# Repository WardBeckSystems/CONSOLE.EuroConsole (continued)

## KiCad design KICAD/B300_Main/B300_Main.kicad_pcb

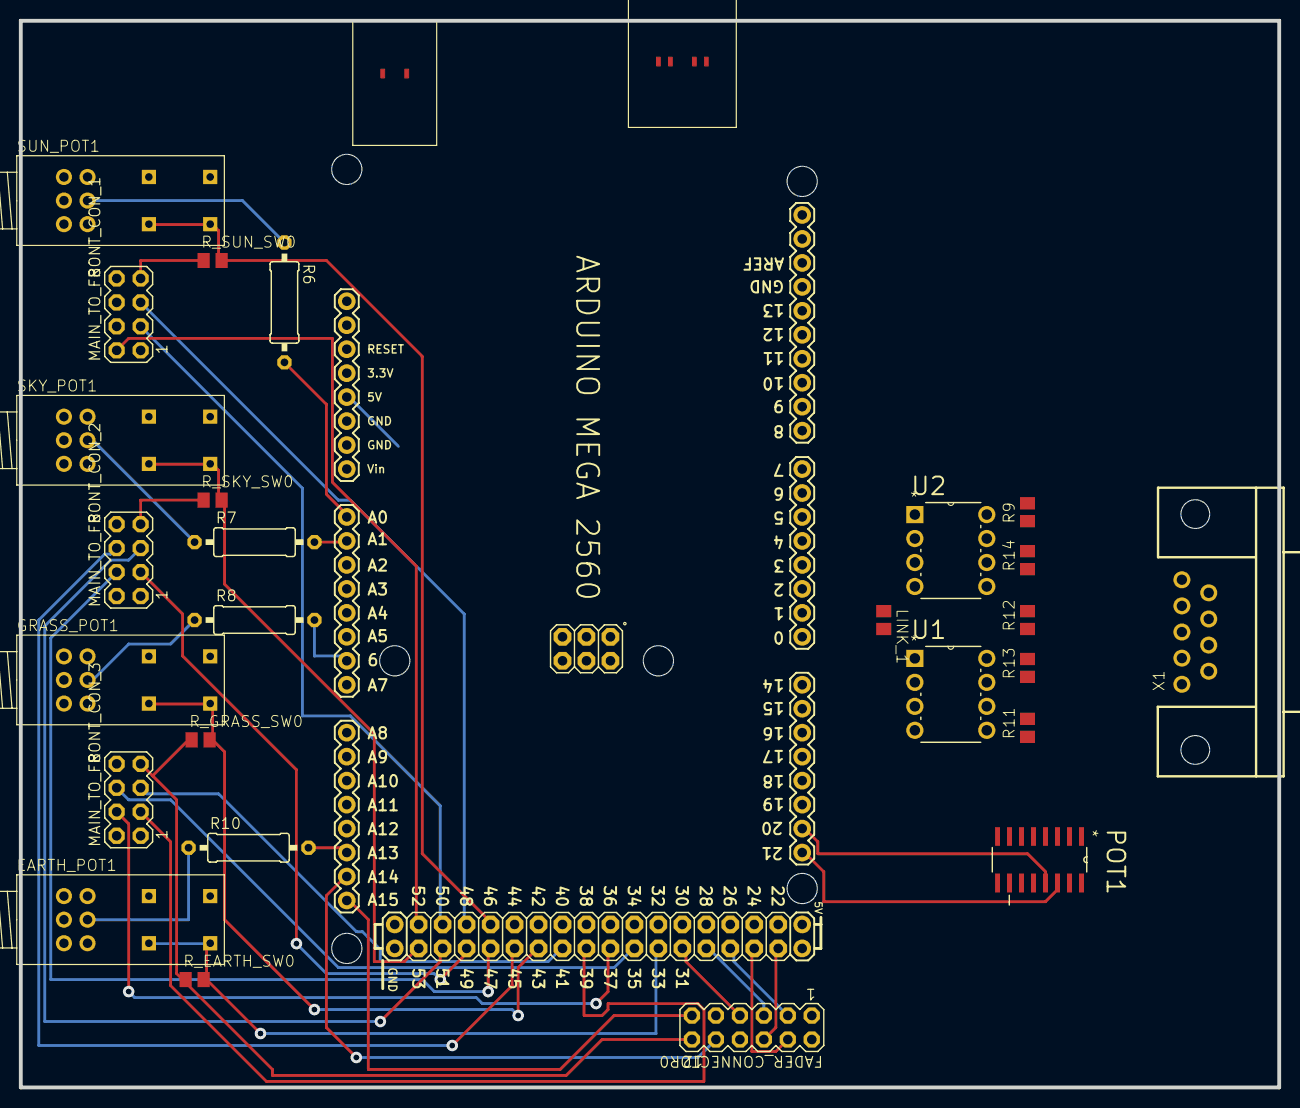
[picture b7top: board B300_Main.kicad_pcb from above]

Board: 2 copper layers, 133.3 x 113.0 mm, 27 parts (0 on the bottom side), 43 nets.

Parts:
EARTH_POT1: WBS_10-081_DUALPOT+DUALSWITCH; WBS_10-081
FADER_CONNECTOR0: MA06-2
GRASS_POT1: WBS_10-081_DUALPOT+DUALSWITCH; WBS_10-081
LINK_1: 0; M0805
MAIN_TO_FRONT_CON_1, MAIN_TO_FRONT_CON_2, MAIN_TO_FRONT_CON_3: MA04-2
PCB1: ARDUINO_MEGA2560
POT1: DS1808Z-050+; SOIC127P600X175-16N
R6, R7, R8, R10: 0309_12
R9, R11, R12, R13, R14: 10K; M0805
R_EARTH_SW0: 10K; M0805
R_GRASS_SW0: 10K; M0805
R_SKY_SW0: 10K; M0805
R_SUN_SW0: 10K; M0805
SKY_POT1: WBS_10-081_DUALPOT+DUALSWITCH; WBS_10-081
SUN_POT1: WBS_10-081_DUALPOT+DUALSWITCH; WBS_10-081
U1, U2: DS75176BN; DIP254P762X508-8
X1: D-SUB9-H3M09RA; H3M09RA

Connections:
+5V: EARTH_POT1.P$6, FADER_CONNECTOR0.12, GRASS_POT1.P$6, MAIN_TO_FRONT_CON_1.7, MAIN_TO_FRONT_CON_1.8, MAIN_TO_FRONT_CON_2.7, MAIN_TO_FRONT_CON_2.8, MAIN_TO_FRONT_CON_3.7, MAIN_TO_FRONT_CON_3.8, PCB1.5V, PCB1.<PWR>+V, POT1.16, R9.2, R12.2, R13.2, R_EARTH_SW0.1, R_GRASS_SW0.1, R_SKY_SW0.1, R_SUN_SW0.1, SKY_POT1.P$6, SUN_POT1.P$6, U1.8, U2.8
A0_FNT_POT_SUN: PCB1.A0, R6.2
A1_FNT_POT_SKY: PCB1.A1, R7.2
A6_FNT_POT_GRASS: PCB1.A6, R8.2
A12_FNT_POT_EARTH: PCB1.A12, R10.2
A14_FDR_POT_POSITION: FADER_CONNECTOR0.10, PCB1.A14
A15_FDR_POT_SLIDE: FADER_CONNECTOR0.11, PCB1.A15
D02_SCI_TX_3RC2: PCB1.2, U2.2, U2.3
D14_SCI_TX3: PCB1.14, U2.4
D15_SCI_RX3: LINK_1.2, PCB1.15, R12.1, U1.1
D20_SCI_I2C_SDA: PCB1.20, POT1.13
D21_SCI_I2C_SCL: PCB1.21, POT1.14
D22_FDR_LED_KEY_ONLY: FADER_CONNECTOR0.8, PCB1.22
D23_FDR_LED_KEY_SEL: FADER_CONNECTOR0.6, PCB1.23
D25_FDR_LED_KEY_CHON: FADER_CONNECTOR0.4, PCB1.25
D27_FDR_KEY_CHON: FADER_CONNECTOR0.3, PCB1.27
D29_FDR_KEY_SEL: FADER_CONNECTOR0.5, PCB1.29
D31_FDR_KEY_ONLY: FADER_CONNECTOR0.7, PCB1.31
D33_FNT_SW_POT_EARTH: EARTH_POT1.P$7, EARTH_POT1.P$9, PCB1.33, R_EARTH_SW0.2
D35_FNT_KEY_GRASS: MAIN_TO_FRONT_CON_3.6, PCB1.35
D37_FNT_KEY_EARTH: MAIN_TO_FRONT_CON_3.4, PCB1.37
D39_FNT_LED_KEY_EARTH: MAIN_TO_FRONT_CON_3.3, PCB1.39
D41_FNT_LED_KEY_GRASS: MAIN_TO_FRONT_CON_3.5, PCB1.41
D43_FNT_SW_POT_GRASS: GRASS_POT1.P$7, GRASS_POT1.P$9, PCB1.43, R_GRASS_SW0.2
D45_FNT_KEY_SUN: MAIN_TO_FRONT_CON_2.6, PCB1.45
D46_FNT_SW_POT_SUN: PCB1.46, R_SUN_SW0.2, SUN_POT1.P$7, SUN_POT1.P$9
D47_FNT_KEY_SKY: MAIN_TO_FRONT_CON_2.4, PCB1.47
D48_FNT_NEO_PIXEL: MAIN_TO_FRONT_CON_1.5, PCB1.48
D49_FNT_LED_KEY_SKY: MAIN_TO_FRONT_CON_2.3, PCB1.49
D50_FNT_LED_KEY_SEL: MAIN_TO_FRONT_CON_1.3, PCB1.50
D51_FNT_LED_KEY_SUN: MAIN_TO_FRONT_CON_2.5, PCB1.51
D52_FNT_KEY_SEL: MAIN_TO_FRONT_CON_1.2, PCB1.52
D53_FNT_SW_POT_SKY: PCB1.53, R_SKY_SW0.2, SKY_POT1.P$7, SKY_POT1.P$9
DB9_RS-485-RX+: R9.1, U1.6, X1.3
DB9_RS-485-RX-: R11.2, U1.7, X1.4
DB9_RS-485-TX+: R13.1, U2.6, X1.1
DB9_RS-485-TX-: R14.2, U2.7, X1.2
GND: EARTH_POT1.P$4, EARTH_POT1.P$8, EARTH_POT1.P$10, FADER_CONNECTOR0.1, GRASS_POT1.P$4, GRASS_POT1.P$8, GRASS_POT1.P$10, MAIN_TO_FRONT_CON_1.1, MAIN_TO_FRONT_CON_2.1, MAIN_TO_FRONT_CON_3.1, PCB1.<PWR>-V, PCB1.GND, PCB1.GND., PCB1.GND.., POT1.1, POT1.7, POT1.9, R11.1, R14.1, SKY_POT1.P$4, SKY_POT1.P$8, SKY_POT1.P$10, SUN_POT1.P$4, SUN_POT1.P$8, SUN_POT1.P$10, U1.2, U1.3, U1.5, U2.5
unnamed: EARTH_POT1.P$5, R10.1
unnamed: R7.1, SKY_POT1.P$5
unnamed: R6.1, SUN_POT1.P$5
unnamed: GRASS_POT1.P$5, R8.1
unnamed: LINK_1.1, U2.1

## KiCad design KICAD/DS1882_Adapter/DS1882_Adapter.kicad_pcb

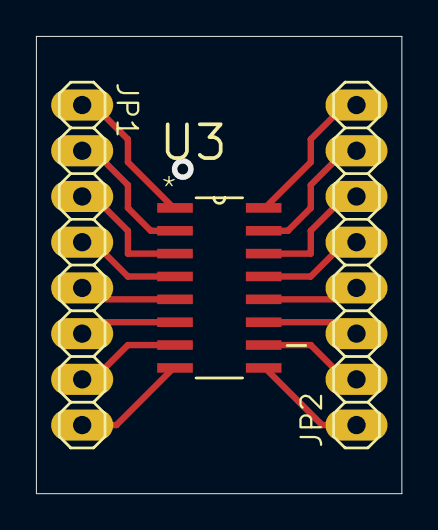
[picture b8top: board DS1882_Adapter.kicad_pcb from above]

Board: 2 copper layers, 20.3 x 25.4 mm, 3 parts (0 on the bottom side), 16 nets.

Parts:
JP1, JP2: 1X08
U3: DS1808Z-050+; SOIC127P600X175-16N

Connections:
unnamed: JP1.1, U3.1
unnamed: JP1.2, U3.2
unnamed: JP1.3, U3.3
unnamed: JP1.4, U3.4
unnamed: JP1.5, U3.5
unnamed: JP1.6, U3.6
unnamed: JP1.7, U3.7
unnamed: JP1.8, U3.8
unnamed: JP2.1, U3.9
unnamed: JP2.2, U3.10
unnamed: JP2.3, U3.11
unnamed: JP2.4, U3.12
unnamed: JP2.5, U3.13
unnamed: JP2.6, U3.14
unnamed: JP2.7, U3.15
unnamed: JP2.8, U3.16
